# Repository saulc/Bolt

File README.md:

# Bolt

Hackaday.io prize 2023 Round 1 Re-engineering Education Finalist.<br>
https://hackaday.io/project/190291-bolt-bots-micro-servo-droids
<br>
Lesson 0 - Teach the teachers how to use github.<br>

 Bolt Botz - Robotics Curriculum Options<br>
 Open Source Hardware, Software and Curriculum!<br>

 Presentation - Show students what Exists Now.<br>
 Build and Interact - Hands on demo are always more engaging and interesting<br>
 Programming - Build on a library(if I write one) or Write Full control code yourself<br>
 Control Circuits - Built a bespoke circuit with an Arduino starter kit or hand soldered project board<br>
 Custom parts and code - Create combine parts and add features.<br>
 Build with Boltz - build something new with a few bolt bits...<br>

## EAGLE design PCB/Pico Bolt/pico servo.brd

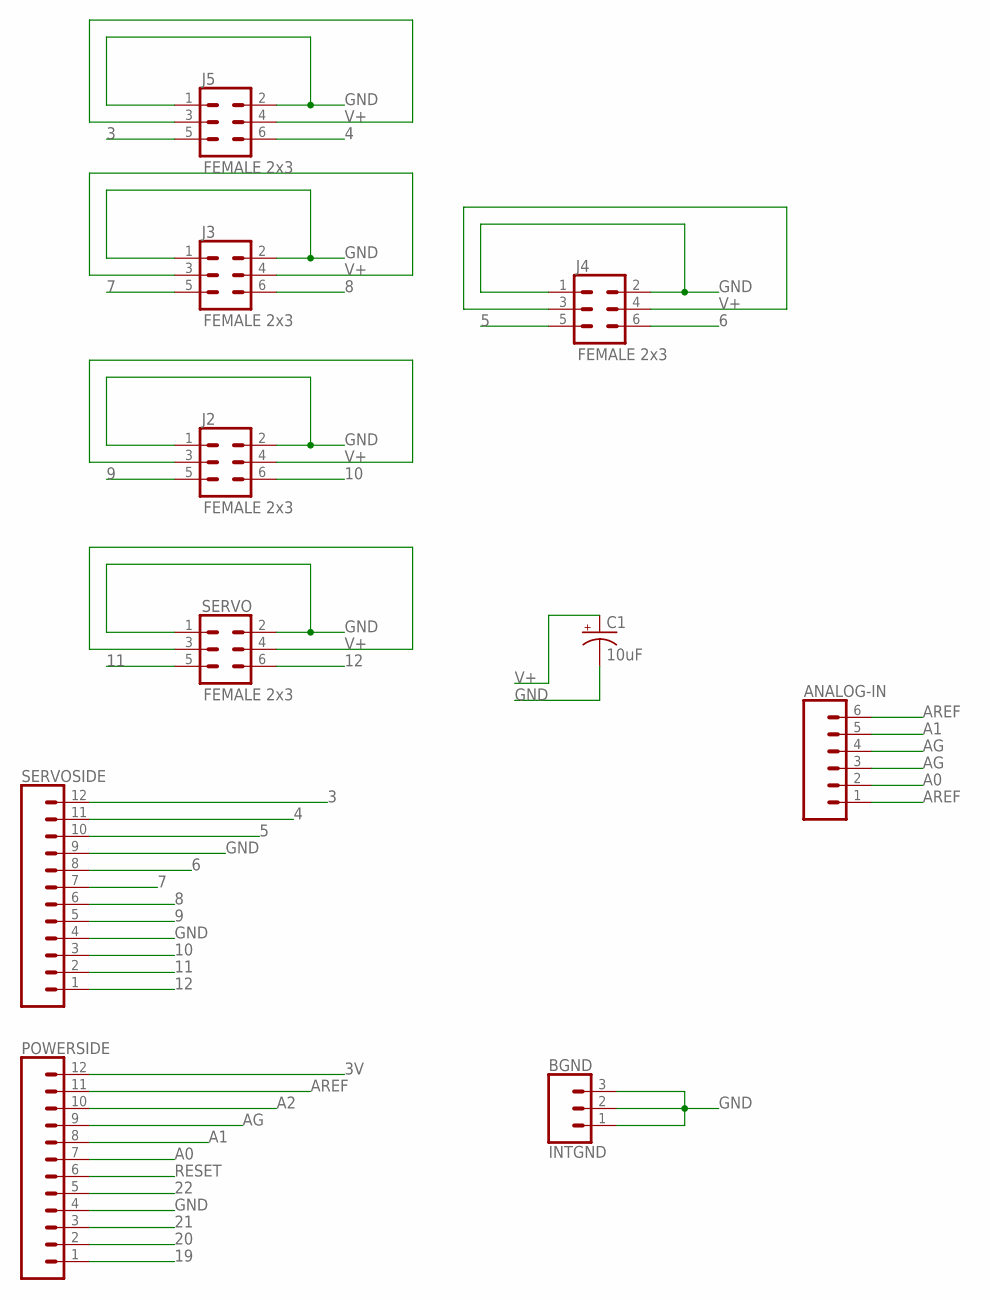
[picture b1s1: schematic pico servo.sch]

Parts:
ANALOG-IN: CONN_06NO_SILK_FEMALE_PTH; 1X06_NO_SILK
BGND: INTGND; 1X03
C1: 10uF; CPOL-RADIAL-2.5MM-5MM
J2, J3, J4, J5: FEMALE 2x3; 2X3
POWERSIDE: CONN_12LONGPADS; 1X12_LONGPADS
SERVO: FEMALE 2x3; 2X3
SERVOSIDE: CONN_12LONGPADS; 1X12_LONGPADS

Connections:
3: J5.5, SERVOSIDE.12
3V: POWERSIDE.12
4: J5.6, SERVOSIDE.11
5: J4.5, SERVOSIDE.10
6: J4.6, SERVOSIDE.8
7: J3.5, SERVOSIDE.7
8: J3.6, SERVOSIDE.6
9: J2.5, SERVOSIDE.5
10: J2.6, SERVOSIDE.3
11: SERVO.5, SERVOSIDE.2
12: SERVO.6, SERVOSIDE.1
19: POWERSIDE.1
20: POWERSIDE.2
21: POWERSIDE.3
22: POWERSIDE.5
A0: ANALOG-IN.2, POWERSIDE.7
A1: ANALOG-IN.5, POWERSIDE.8
A2: POWERSIDE.10
AG: ANALOG-IN.3, ANALOG-IN.4, POWERSIDE.9
AREF: ANALOG-IN.1, ANALOG-IN.6, POWERSIDE.11
GND: BGND.1, BGND.2, BGND.3, C1.2 (-), J2.1, J2.2, J3.1, J3.2, J4.1, J4.2, J5.1, J5.2, POWERSIDE.4, SERVO.1, SERVO.2, SERVOSIDE.4, SERVOSIDE.9
RESET: POWERSIDE.6
V+: C1.1 (+), J2.3, J2.4, J3.3, J3.4, J4.3, J4.4, J5.3, J5.4, SERVO.3, SERVO.4

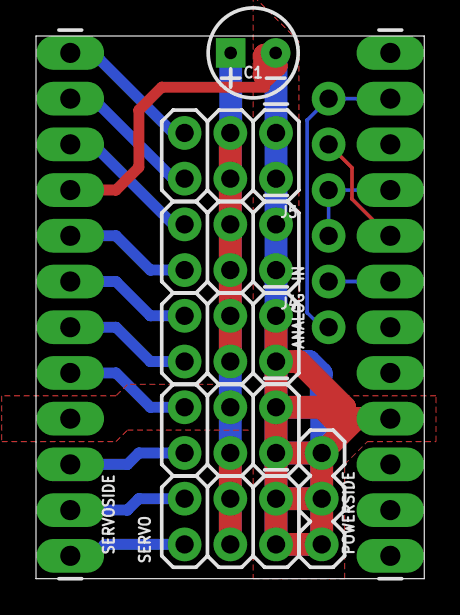
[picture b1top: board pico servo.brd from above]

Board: 2 copper layers, 21.6 x 30.1 mm, 10 parts (0 on the bottom side), 16 nets.

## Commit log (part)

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2023-04-22 design files
    ...
2023-04-26 Tone Wheel Test
    servo interferance...
2023-04-26 scorpion
    code name banchii
2023-04-28 tone test
    small update.. speed is good!
2023-05-01 curved ducts
    ...
2023-05-02 toroidal propeller
    kinda...v1
2023-05-02 tor
    donuts, still no thrust..
2023-05-03 drawbot test on pico
    more speed = less skips?
2023-05-11 drawbot
    stepservo class
2023-05-13 bubbles
    and readme update.
2023-05-13 ..
    read me formatting?
2023-05-13 readme
    format..
2023-05-13 Pico servo board
    ...nrf servo board base
2023-05-13 needs labels
    extend to vsys(vin?)
2023-05-15 rz
    no more car for now...
2023-07-07 box bot
    ....

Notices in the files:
parts and their libraries:
SparkFun-Connectors: Licensing: Creative Commons ShareAlike 4.0 International - https://creativecommons.org/licenses/by-sa/4.0
